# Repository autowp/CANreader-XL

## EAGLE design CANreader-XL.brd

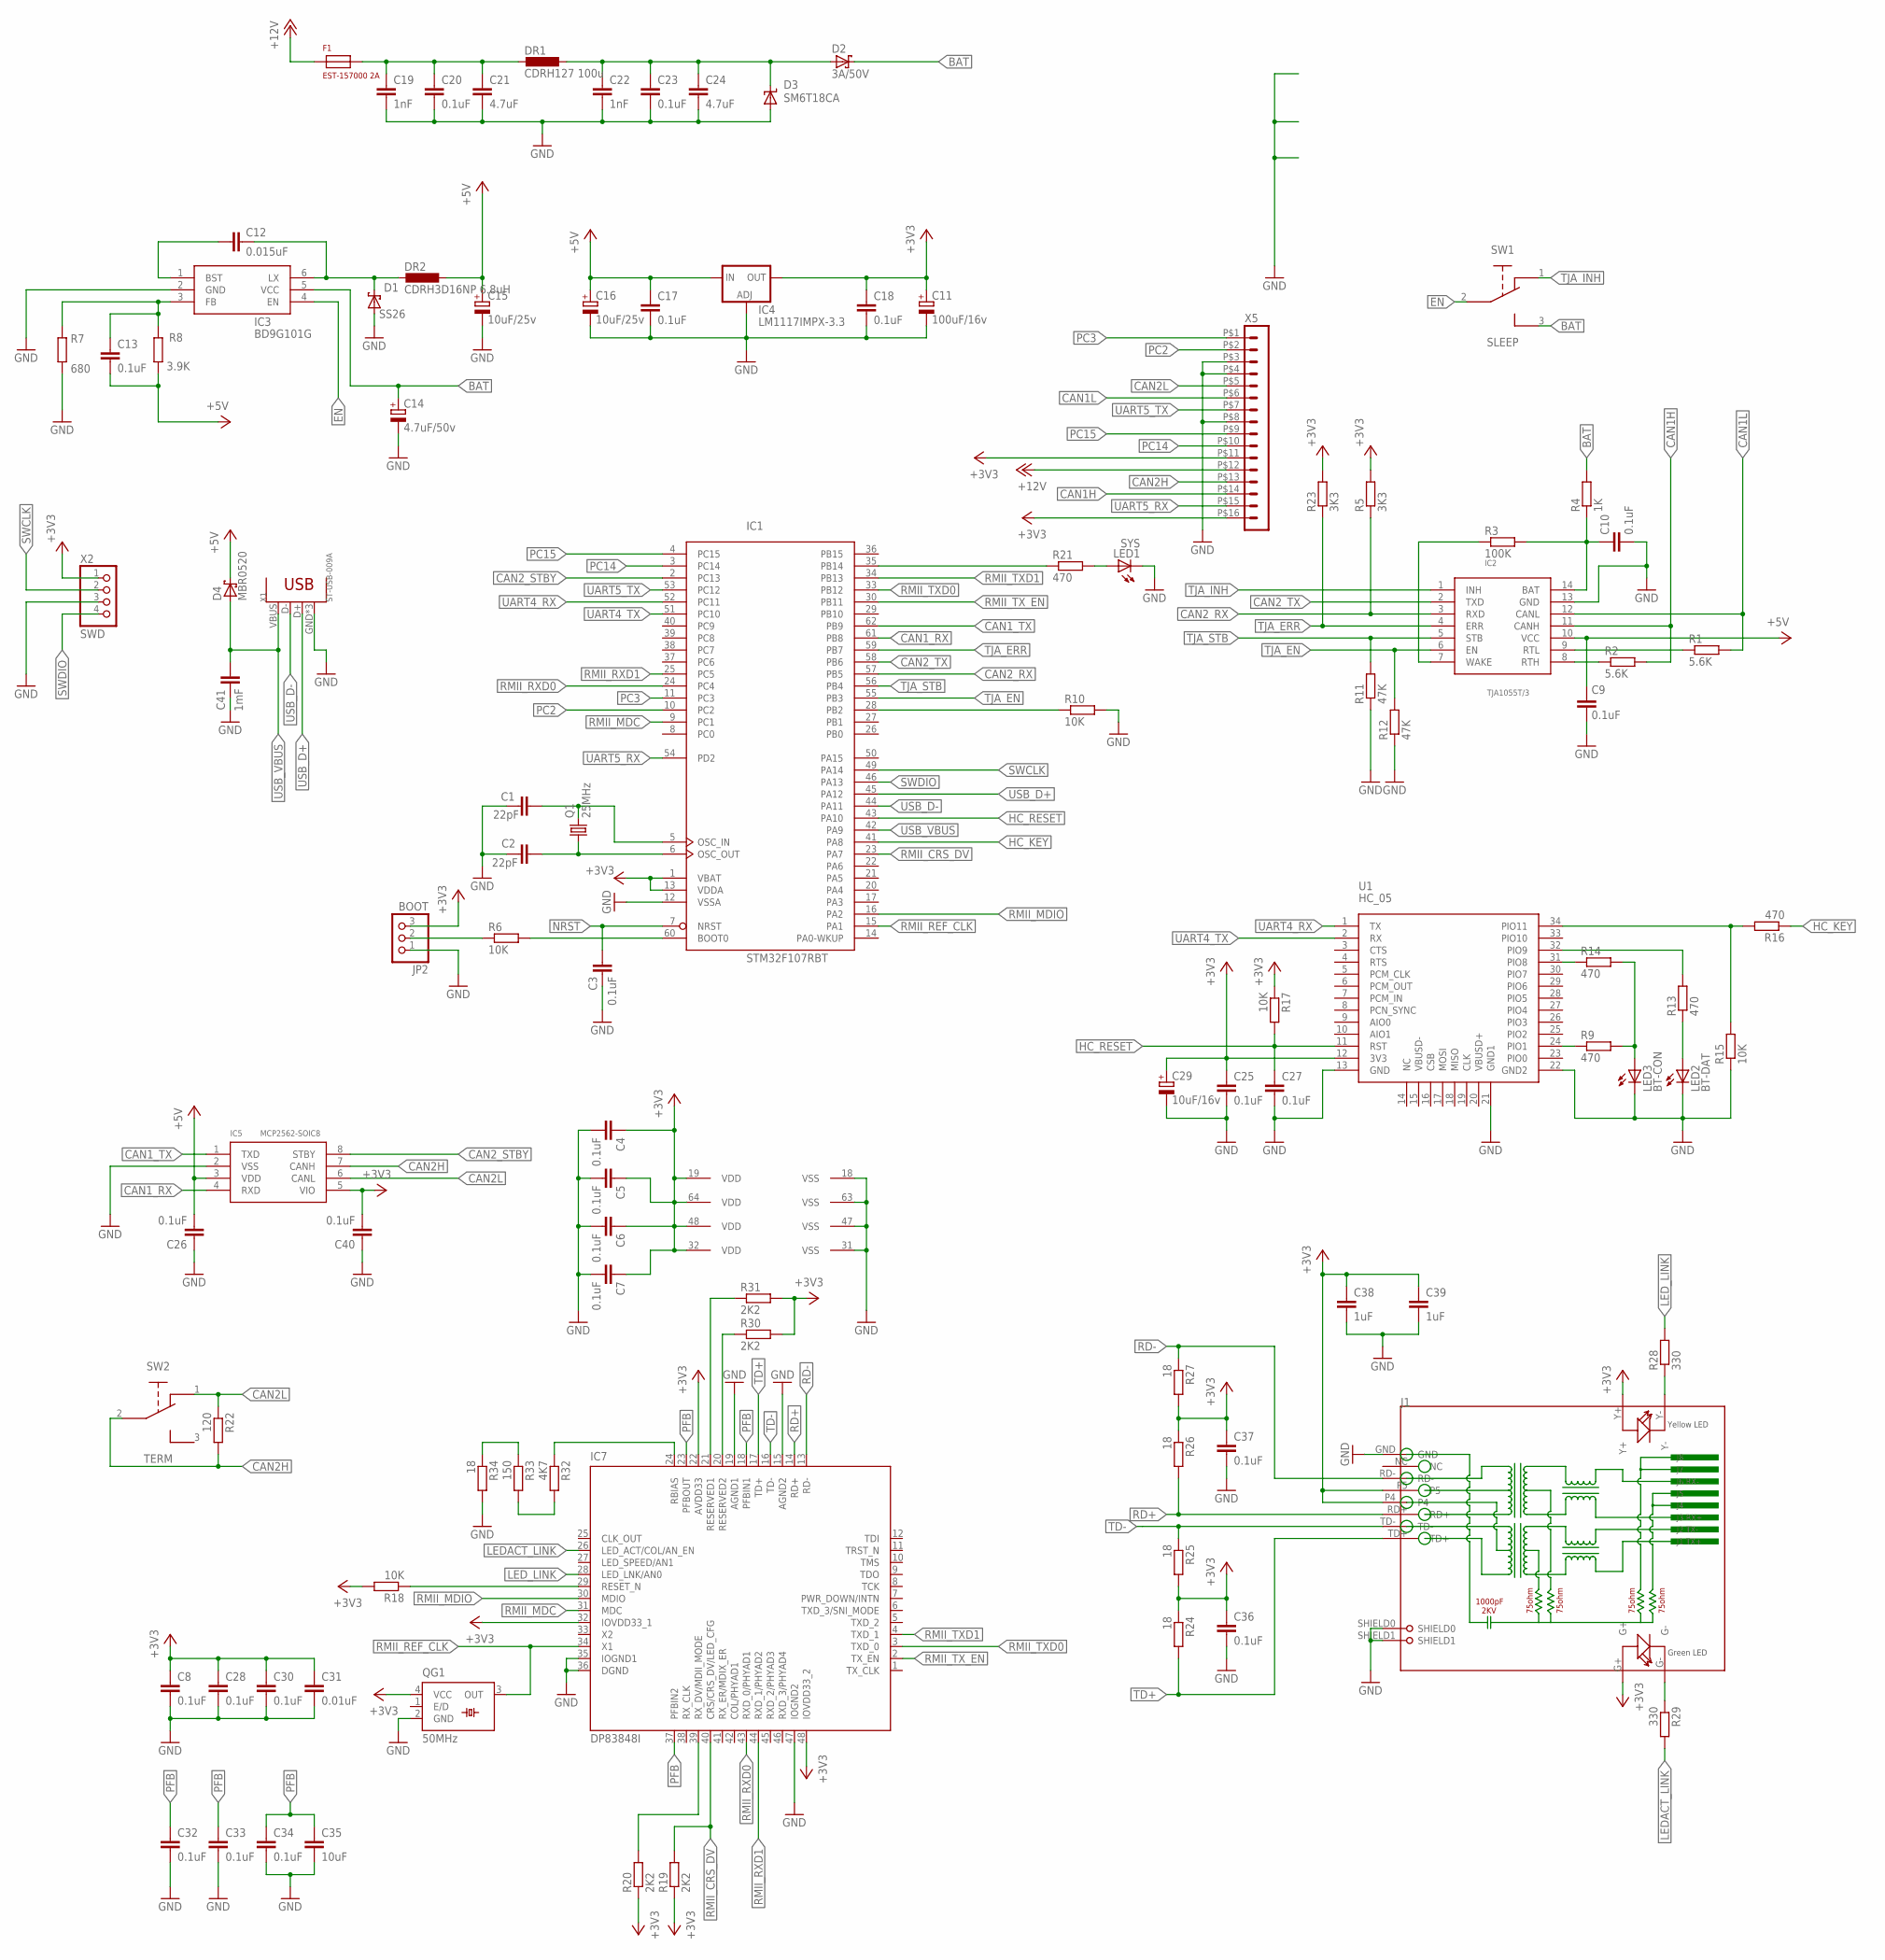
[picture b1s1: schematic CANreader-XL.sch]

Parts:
C1, C2: 22pF; C0805
C3, C4, C5, C6, C7, C8, C9, C10, C13, C17, C18, C20, C23, C25, C26, C27, C28, C30, C32, C33, C34, C36, C37, C40: 0.1uF; C0805
C11: 100uF/16v; SMC_D
C12: 0.015uF; C0805
C14: 4.7uF/50v; 153CLV-0505
C15, C16: 10uF/25v; SMC_C
C19, C22: 1nF; C0805
C21, C24: 4.7uF; C0805
C29: 10uF/16v; SMC_A
C31: 0.01uF; C0805
C35: 10uF; C0805
C38, C39: 1uF; C0805
C41: 1mF; C0805
D1: SS26; SMB
D2: 3A/50V; SMC
D3: SM6T18CA; SMBJ
D4: MBR0520; SOD123
DR1: CDRH127 100u; MS85
DR2: CDRH3D16NP 6.8uH; CDRH3D16NP
F1: EST-157000 2A; FUSE
IC1: STM32F107RBT; LQFP64
IC2: TJA1055T/3; SO-14W
IC3: BD9G101G; SSOP6
IC4: LM1117IMPX-3.3; SOT223
IC5: MCP2562-SOIC8; SOIC8-1.27-5X4MM
IC7: DP83848I; LQFP48
J1: RJ45-HR911105A-HR911105A; RJ45
JP2: BOOT; 1X03
LED1: SYS; LED3MM
LED2: BT-DAT; LED3MM
LED3: BT-CON; LED3MM
Q1: 25MHz; HC49/S
QG1: 50MHz; SM77H
R1, R2: 5.6K; R0805
R3: 100K; R0805
R4: 1K; R0805
R5, R23: 3K3; R0805
R6, R10, R15, R17, R18: 10K; R0805
R7: 680; R0805
R8: 3.9K; R0805
R9, R13, R14, R16, R21: 470; R0805
R11, R12: 47K; R0805
R19, R20, R30, R31: 2K2; R0805
R22: 120; R0805
R24, R25, R26, R27, R34: 18; R0805
R28, R29: 330; R0805
R32: 4K7; R0805
R33: 150; R0805
SW1: SLEEP; SS12F27
SW2: TERM; SS12F27
U1: HC_05; BLUETOOTH_SMD
X1: ST-USB-009A; USB4+2-2.5-90D
X2: SWD; 1X04
X5: HEADER_POS16_43045-1600; 43045-1600

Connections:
+3V3: C4.1, C5.1, C6.1, C7.1, C8.1, C11.+, C18.1, C25.1, C28.1, C29.+, C30.1, C31.1, C36.1, C37.1, C38.1, C39.1, C40.2, IC1.1 (VBAT), IC1.13 (VDDA), IC1.19 (VDD), IC1.32 (VDD), IC1.48 (VDD), IC1.64 (VDD), IC4.2 (OUT), IC4.4 (OUT), IC5.5 (VIO), IC7.22 (AVDD33), IC7.32 (IOVDD33_1), IC7.48 (IOVDD33_2), J1.G+, J1.P4, J1.P5, J1.Y+, JP2.3, QG1.4 (VCC), R5.2, R17.1, R18.2, R19.1, R20.1, R23.2, R24.1, R25.2, R26.1, R27.2, R30.2, R31.2, U1.12 (3V3), X2.1, X5.P$11 (11), X5.P$16 (16)
+5V: C9.1, C13.2, C15.+, C16.+, C17.1, C26.2, D4.C, DR2.P$2 (2), IC2.10 (VCC), IC4.3 (IN), IC5.3 (VDD), R8.1
+12V: F1.P$1 (1), X5.P$12 (12)
BAT: C14.+, D2.C, IC3.5 (VCC), R4.2, SW1.3
BAT1: C22.1, C23.1, C24.1, D2.A, D3.C, DR1.P$2 (2)
BD9-FB: C13.1, IC3.3 (FB), R7.2, R8.2
CAN1H: IC2.11 (CANH), R2.2, X5.P$14 (14)
CAN1L: IC2.12 (CANL), R1.2, X5.P$6 (6)
CAN1_RX: IC1.61 (PB8), IC5.4 (RXD)
CAN1_TX: IC1.62 (PB9), IC5.1 (TXD)
CAN2H: IC5.7 (CANH), R22.2, SW2.2, X5.P$13 (13)
CAN2L: IC5.6 (CANL), R22.1, SW2.1, X5.P$5 (5)
CAN2_RX: IC1.57 (PB5), IC2.3 (RXD), R5.1
CAN2_STBY: IC1.2 (PC13), IC5.8 (STBY)
CAN2_TX: IC1.58 (PB6), IC2.2 (TXD)
EN: IC3.4 (EN), SW1.2
GND: C1.2, C2.2, C3.1, C4.2, C5.2, C6.2, C7.2, C8.2, C9.2, C10.2, C11.-, C14.-, C15.-, C16.-, C17.2, C18.2, C19.2, C20.2, C21.2, C22.2, C23.2, C24.2, C25.2, C26.1, C27.2, C28.2, C29.-, C30.2, C31.2, C32.2, C33.2, C34.2, C35.2, C36.2, C37.2, C38.2, C39.2, C40.1, C41.2, D1.A, D3.A, IC1.12 (VSSA), IC1.18 (VSS), IC1.31 (VSS), IC1.47 (VSS), IC1.63 (VSS), IC2.13 (GND), IC3.2 (GND), IC4.1 (ADJ), IC5.2 (VSS), IC7.15 (AGND2), IC7.19 (AGND1), IC7.35 (IOGND1), IC7.36 (DGND), IC7.47 (IOGND2), J1.GND, J1.SHIELD0, J1.SHIELD1, JP2.1, LED1.K (C), LED2.K (C), LED3.K (C), QG1.2 (GND), R7.1, R10.2, R11.1, R12.1, R15.1, R34.2, U1.13 (GND), U1.21 (GND1), U1.22 (GND2), X1.GND (4), X1.S1 (4), X1.S2 (4), X2.3, X5.P$3 (3), X5.P$4 (4), X5.P$8 (8)
HC_KEY: IC1.41 (PA8), R16.1
HC_RESET: C27.1, IC1.43 (PA10), R17.2, U1.11 (RST)
LEDACT_LINK: IC7.26 (LED_ACT/COL/AN_EN), R29.2
LED_LINK: IC7.28 (LED_LNK/AN0), R28.2
unnamed: C1.1, IC1.5 (OSC_IN), Q1.2
unnamed: C2.1, IC1.6 (OSC_OUT), Q1.1
unnamed: IC1.60 (BOOT0), R6.2
unnamed: IC1.28 (PB2), R10.1
unnamed: R14.1, U1.31 (PIO8)
unnamed: IC1.35 (PB14), R21.1
unnamed: IC2.8 (RTH), R2.1
unnamed: IC2.9 (RTL), R1.1
unnamed: C12.1, IC3.1 (BST)
unnamed: R13.2, U1.32 (PIO9)
unnamed: LED2.A, R13.1
unnamed: C12.2, D1.C, DR2.P$1 (1), IC3.6 (LX)
unnamed: R9.1, U1.24 (PIO1)
unnamed: LED1.A, R21.2
unnamed: IC7.29 (RESET_N), R18.1
unnamed: IC7.20 (RESERVED2), R30.1
unnamed: C19.1, C20.1, C21.1, DR1.P$1 (1), F1.P$2 (2)
unnamed: IC7.39 (RX_DV/MDII_MODE), R20.2
unnamed: IC7.21 (RESERVED1), R31.1
unnamed: J1.G-, R29.1
unnamed: J1.Y-, R28.1
unnamed: R15.2, R16.2, U1.34 (PIO11)
unnamed: IC7.24 (RBIAS), R32.1
unnamed: R32.2, R33.2
unnamed: R33.1, R34.1
unnamed: JP2.2, R6.1
unnamed: LED3.A, R9.2, R14.2
NRST: C3.2, IC1.7 (NRST)
PC2: IC1.10 (PC2), X5.P$2 (2)
PC3: IC1.11 (PC3), X5.P$1 (1)
PC14: IC1.3 (PC14), X5.P$10 (10)
PC15: IC1.4 (PC15), X5.P$9 (9)
PFB: C32.1, C33.1, C34.1, C35.1, IC7.18 (PFBIN1), IC7.23 (PFBOUT), IC7.37 (PFBIN2)
RD+: IC7.14 (RD+), J1.RD+, R26.2
RD-: IC7.13 (RD-), J1.RD-, R27.1
RMII_CRS_DV: IC1.23 (PA7), IC7.40 (CRS/CRS_DV/LED_CFG), R19.2
RMII_MDC: IC1.9 (PC1), IC7.31 (MDC)
RMII_MDIO: IC1.16 (PA2), IC7.30 (MDIO)
RMII_REF_CLK: IC1.15 (PA1), IC7.34 (X1), QG1.3 (OUT)
RMII_RXD0: IC1.24 (PC4), IC7.43 (RXD_0/PHYAD1)
RMII_RXD1: IC1.25 (PC5), IC7.44 (RXD_1/PHYAD2)
RMII_TXD0: IC1.33 (PB12), IC7.3 (TXD_0)
RMII_TXD1: IC1.34 (PB13), IC7.4 (TXD_1)
RMII_TX_EN: IC1.30 (PB11), IC7.2 (TX_EN)
SWCLK: IC1.49 (PA14), X2.2
SWDIO: IC1.46 (PA13), X2.4
TD+: IC7.17 (TD+), J1.TD+, R24.2
TD-: IC7.16 (TD-), J1.TD-, R25.1
TJABAT: C10.1, IC2.14 (BAT), R3.2, R4.1
TJAWAKE: IC2.7 (WAKE), R3.1
TJA_EN: IC1.55 (PB3), IC2.6 (EN), R12.2
TJA_ERR: IC1.59 (PB7), IC2.4 (ERR), R23.1
TJA_INH: IC2.1 (INH), SW1.1
TJA_STB: IC1.56 (PB4), IC2.5 (STB), R11.2
UART4_RX: IC1.52 (PC11), U1.1 (TX)
UART4_TX: IC1.51 (PC10), U1.2 (RX)
UART5_RX: IC1.54 (PD2), X5.P$15 (15)
UART5_TX: IC1.53 (PC12), X5.P$7 (7)
USB_D+: IC1.45 (PA12), X1.D+ (3)
USB_D-: IC1.44 (PA11), X1.D- (2)
USB_VBUS: C41.1, D4.A, IC1.42 (PA9), X1.VBUS (1)

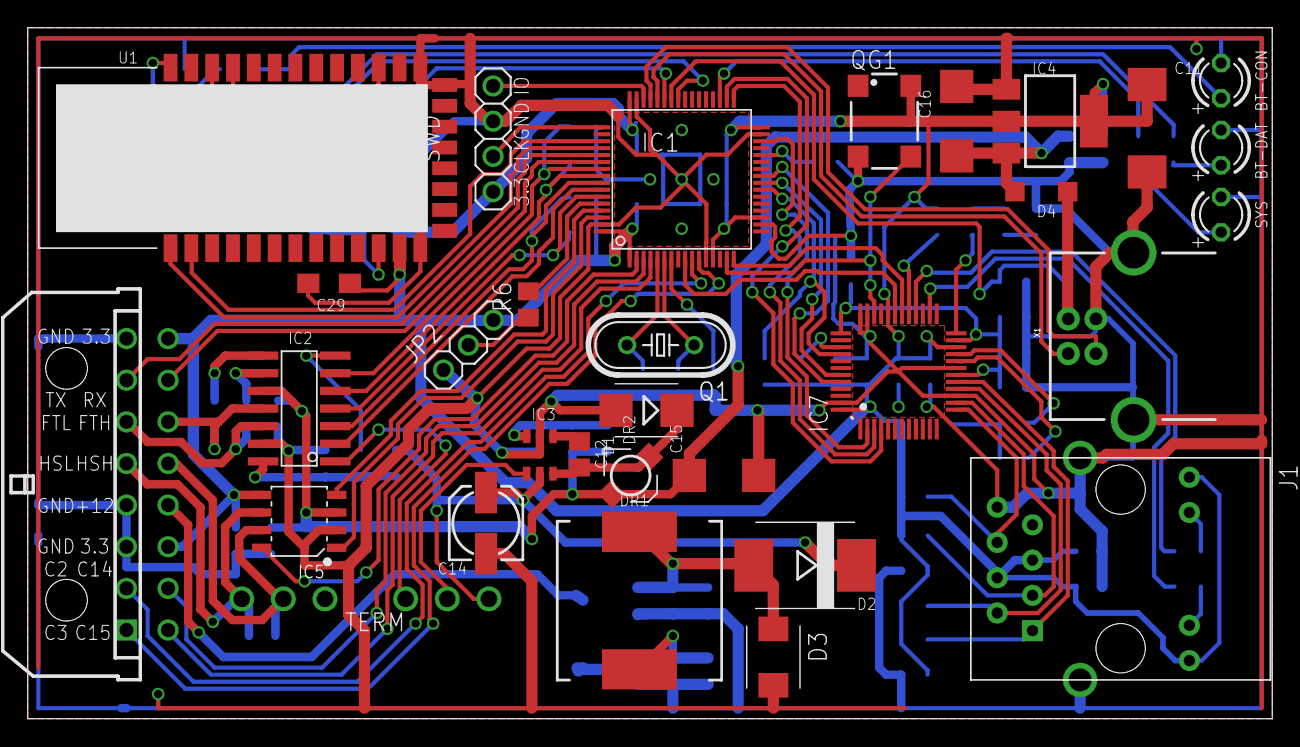
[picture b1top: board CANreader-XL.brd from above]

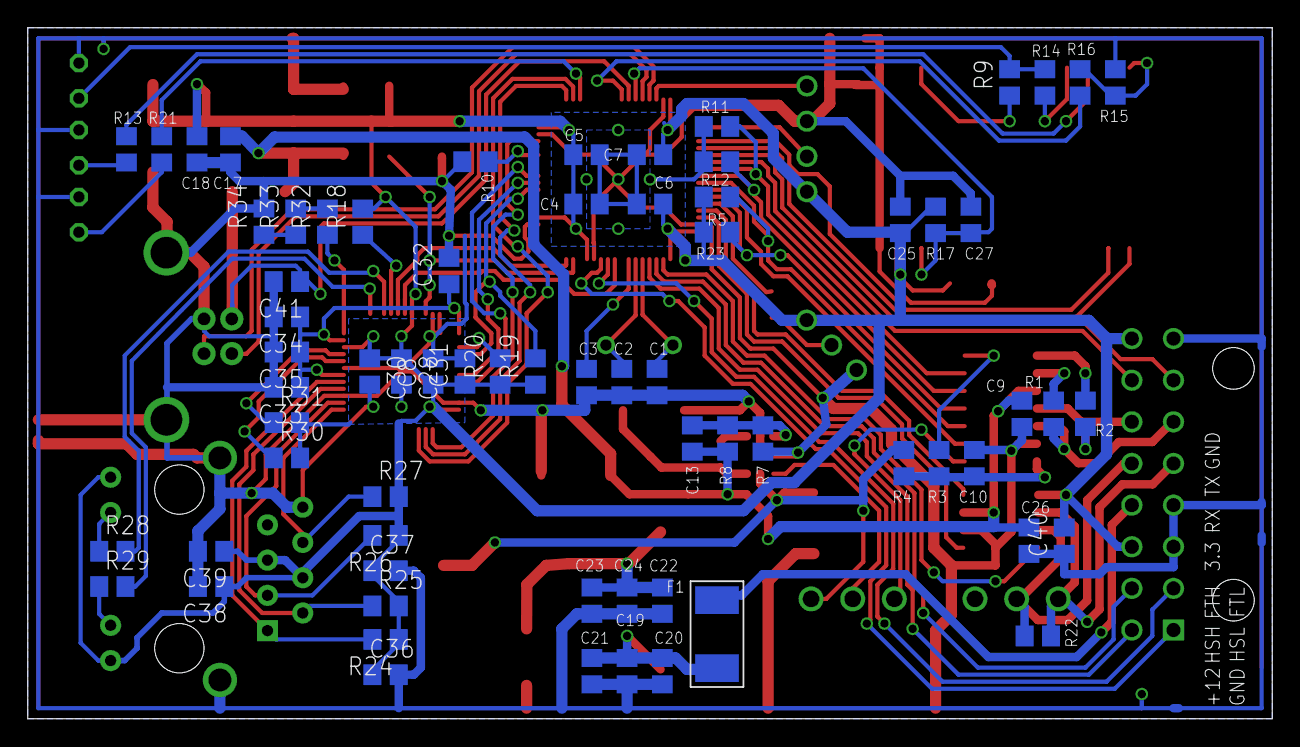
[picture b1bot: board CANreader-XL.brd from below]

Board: 2 copper layers, 89.7 x 49.8 mm, 101 parts (69 on the bottom side), 82 nets.

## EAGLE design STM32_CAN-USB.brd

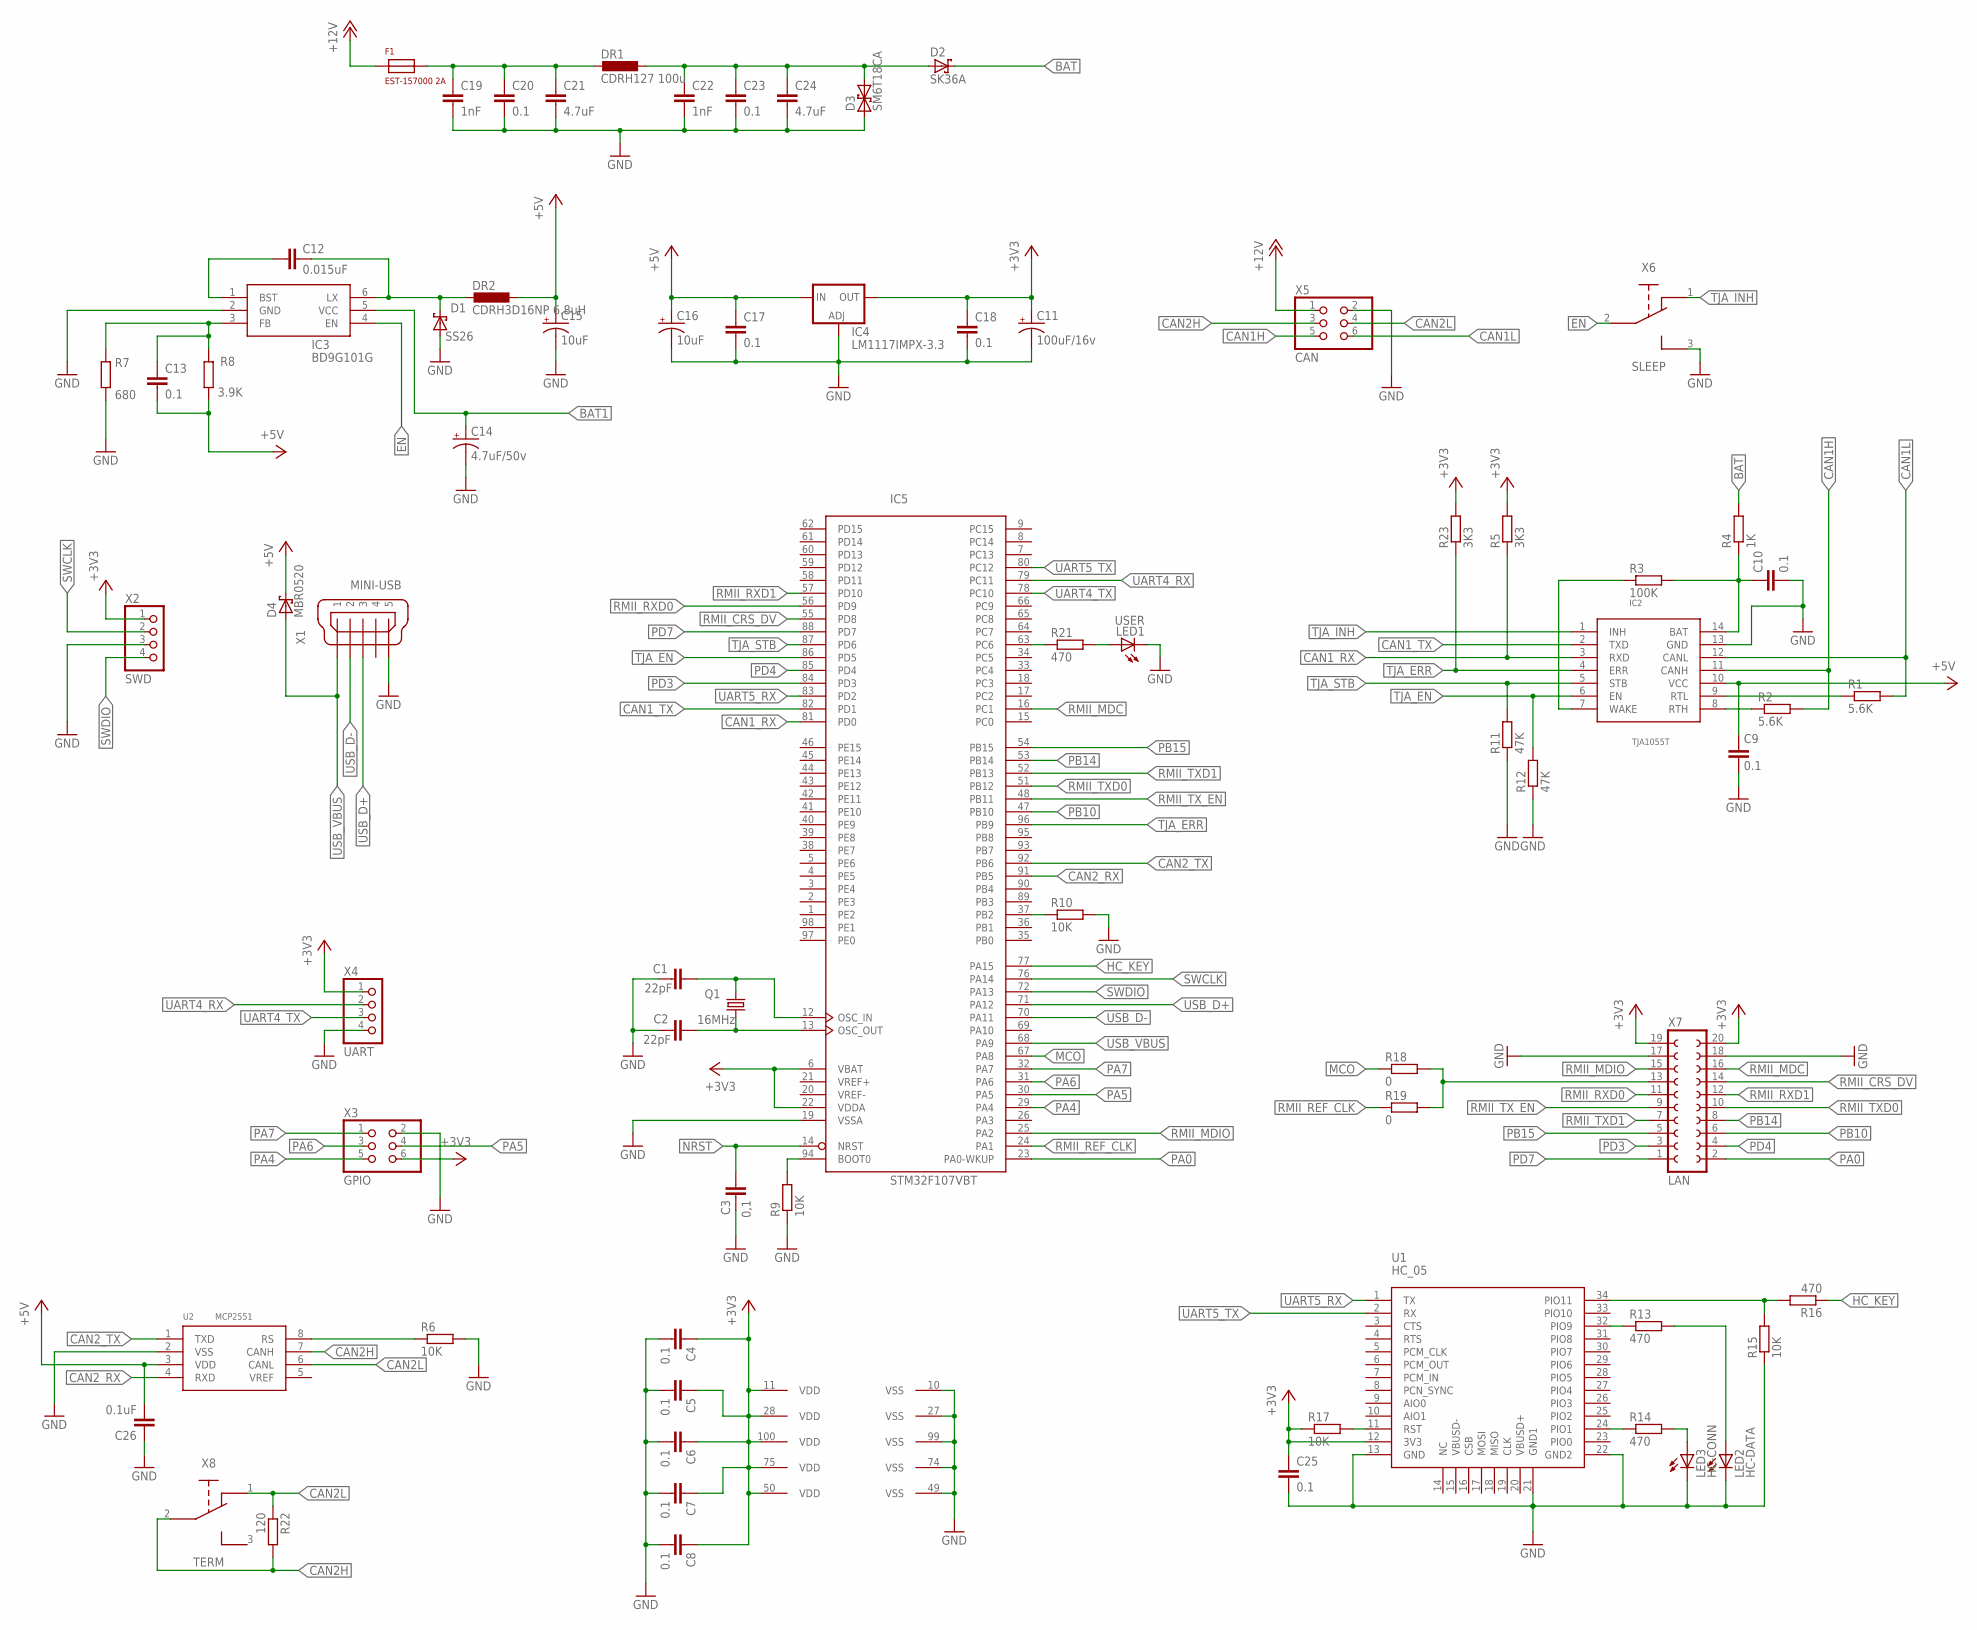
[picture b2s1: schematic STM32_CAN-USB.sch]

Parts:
C1, C2: 22pF; C0805
C3: 0,1; C0805
C4, C5, C6, C7, C8, C9, C10, C13, C17, C18, C20, C23, C25: 0.1; C0805
C11: 100uF/16v; 153CLV-0605
C12: 0.015uF; C0805
C14: 4.7uF/50v; 153CLV-0605
C15, C16: 10uF; 153CLV-0605
C19, C22: 1nF; C0805
C21, C24: 4.7uF; C0805
C26: 0.1uF; C0805
D1: SS26; SMB
D2: SK36A; DO-214AC
D3: SM6T18CA; DO214AA
D4: MBR0520; SOD123
DR1: CDRH127 100u; MS85
DR2: CDRH3D16NP 6.8uH; CDRH3D16NP
F1: EST-157000 2A; FUSE
IC2: TJA1055T; SO-14W
IC3: BD9G101G; SSOP6
IC4: LM1117IMPX-3.3; SOT223
IC5: STM32F107VBT; LQFP100
LED1: USER; LED3MM
LED2: HC-DATA; LED3MM
LED3: HC-CONN; LED3MM
Q1: 16MHz; HC49UP
R1, R2: 5.6K; R0805
R3: 100K; R0805
R4: 1K; R0805
R5, R23: 3K3; R0805
R6, R9, R10, R15, R17: 10K; R0805
R7: 680; R0805
R8: 3.9K; R0805
R11, R12: 47K; R0805
R13, R14, R16, R21: 470; R0805
R18, R19: 0; R0805
R22: 120; R0805
U1: HC_05; BLUETOOTH_SMD
U2: MCP2551; SO08
X1: MINI-USB; UX60-MB-5ST
X2: SWD; 1X04
X3: GPIO; 2X03/90
X4: UART; 1X04/90
X5: CAN; 2X03/90
X6: SLEEP; SS12F27
X7: LAN; FE10-2W
X8: TERM; SS12F27

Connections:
+3V3: C4.1, C5.1, C6.1, C7.1, C8.1, C11.+, C18.1, C25.1, IC4.2 (OUT), IC4.4 (OUT), IC5.6 (VBAT), IC5.11 (VDD), IC5.22 (VDDA), IC5.28 (VDD), IC5.50 (VDD), IC5.75 (VDD), IC5.100 (VDD), R5.2, R17.1, R23.2, U1.12 (3V3), X2.1, X3.6, X4.1, X7.19, X7.20
+5V: C9.1, C13.2, C15.+, C16.+, C17.1, C26.2, D4.C, DR2.P$2 (2), IC2.10 (VCC), IC4.3 (IN), R8.1, U2.3 (VDD)
+12V: F1.P$1 (1), X5.1
BAT: D2.C, R4.2
BAT1: C14.+, C22.1, C23.1, C24.1, D2.A, D3.C (2), DR1.P$2 (2), IC3.5 (VCC)
BD9-FB: C13.1, IC3.3 (FB), R7.2, R8.2
CAN1H: IC2.11 (CANH), R2.2, X5.5
CAN1L: IC2.12 (CANL), R1.2, X5.6
CAN1_RX: IC2.3 (RXD), IC5.81 (PD0), R5.1
CAN1_TX: IC2.2 (TXD), IC5.82 (PD1)
CAN2H: R22.2, U2.7 (CANH), X5.3, X8.2
CAN2L: R22.1, U2.6 (CANL), X5.4, X8.1
CAN2_RX: IC5.91 (PB5), U2.4 (RXD)
CAN2_TX: IC5.92 (PB6), U2.1 (TXD)
EN: IC3.4 (EN), X6.2
GND: C1.2, C2.2, C3.1, C4.2, C5.2, C6.2, C7.2, C8.2, C9.2, C10.2, C11.-, C14.-, C15.-, C16.-, C17.2, C18.2, C19.2, C20.2, C21.2, C22.2, C23.2, C24.2, C25.2, C26.1, D1.A, D3.A (1), IC2.13 (GND), IC3.2 (GND), IC4.1 (ADJ), IC5.10 (VSS), IC5.19 (VSSA), IC5.27 (VSS), IC5.49 (VSS), IC5.74 (VSS), IC5.99 (VSS), LED1.K (C), LED2.K (C), LED3.K (C), R6.2, R7.1, R9.1, R10.2, R11.1, R12.1, R15.1, U1.13 (GND), U1.21 (GND1), U1.22 (GND2), U2.2 (VSS), X1.5, X1.M1 (5), X1.M2 (5), X2.3, X3.2, X4.4, X5.2, X6.3, X7.17, X7.18
HC_KEY: IC5.77 (PA15), R16.1
MCO: IC5.67 (PA8), R18.1
unnamed: C1.1, IC5.12 (OSC_IN), Q1.2
unnamed: C2.1, IC5.13 (OSC_OUT), Q1.1
unnamed: IC5.94 (BOOT0), R9.2
unnamed: IC5.37 (PB2), R10.1
unnamed: R6.1, U2.8 (RS)
unnamed: IC5.63 (PC6), R21.1
unnamed: IC2.8 (RTH), R2.1
unnamed: IC2.9 (RTL), R1.1
unnamed: C12.1, IC3.1 (BST)
unnamed: C12.2, D1.C, DR2.P$1 (1), IC3.6 (LX)
unnamed: LED1.A, R21.2
unnamed: C19.1, C20.1, C21.1, DR1.P$1 (1), F1.P$2 (2)
unnamed: R13.1, U1.32 (PIO9)
unnamed: R14.1, U1.24 (PIO1)
unnamed: LED2.A, R13.2
unnamed: LED3.A, R14.2
unnamed: R17.2, U1.11 (RST)
unnamed: R15.2, R16.2, U1.34 (PIO11)
unnamed: R18.2, R19.2, X7.13
NRST: C3.2, IC5.14 (NRST)
PA0: IC5.23 (PA0-WKUP), X7.2
PA4: IC5.29 (PA4), X3.5
PA5: IC5.30 (PA5), X3.4
PA6: IC5.31 (PA6), X3.3
PA7: IC5.32 (PA7), X3.1
PB10: IC5.47 (PB10), X7.6
PB14: IC5.53 (PB14), X7.8
PB15: IC5.54 (PB15), X7.5
PD3: IC5.84 (PD3), X7.3
PD4: IC5.85 (PD4), X7.4
PD7: IC5.88 (PD7), X7.1
RMII_CRS_DV: IC5.55 (PD8), X7.14
RMII_MDC: IC5.16 (PC1), X7.16
RMII_MDIO: IC5.25 (PA2), X7.15
RMII_REF_CLK: IC5.24 (PA1), R19.1
RMII_RXD0: IC5.56 (PD9), X7.11
RMII_RXD1: IC5.57 (PD10), X7.12
RMII_TXD0: IC5.51 (PB12), X7.10
RMII_TXD1: IC5.52 (PB13), X7.7
RMII_TX_EN: IC5.48 (PB11), X7.9
SWCLK: IC5.76 (PA14), X2.2
SWDIO: IC5.72 (PA13), X2.4
TJABAT: C10.1, IC2.14 (BAT), R3.2, R4.1
TJAWAKE: IC2.7 (WAKE), R3.1
TJA_EN: IC2.6 (EN), IC5.86 (PD5), R12.2
TJA_ERR: IC2.4 (ERR), IC5.96 (PB9), R23.1
TJA_INH: IC2.1 (INH), X6.1
TJA_STB: IC2.5 (STB), IC5.87 (PD6), R11.2
UART4_RX: IC5.79 (PC11), X4.2
UART4_TX: IC5.78 (PC10), X4.3
UART5_RX: IC5.83 (PD2), U1.1 (TX)
UART5_TX: IC5.80 (PC12), U1.2 (RX)
USB_D+: IC5.71 (PA12), X1.3
USB_D-: IC5.70 (PA11), X1.2
USB_VBUS: D4.A, IC5.68 (PA9), X1.1
VREF+: IC5.21 (VREF+)
VREF-: IC5.20 (VREF-)

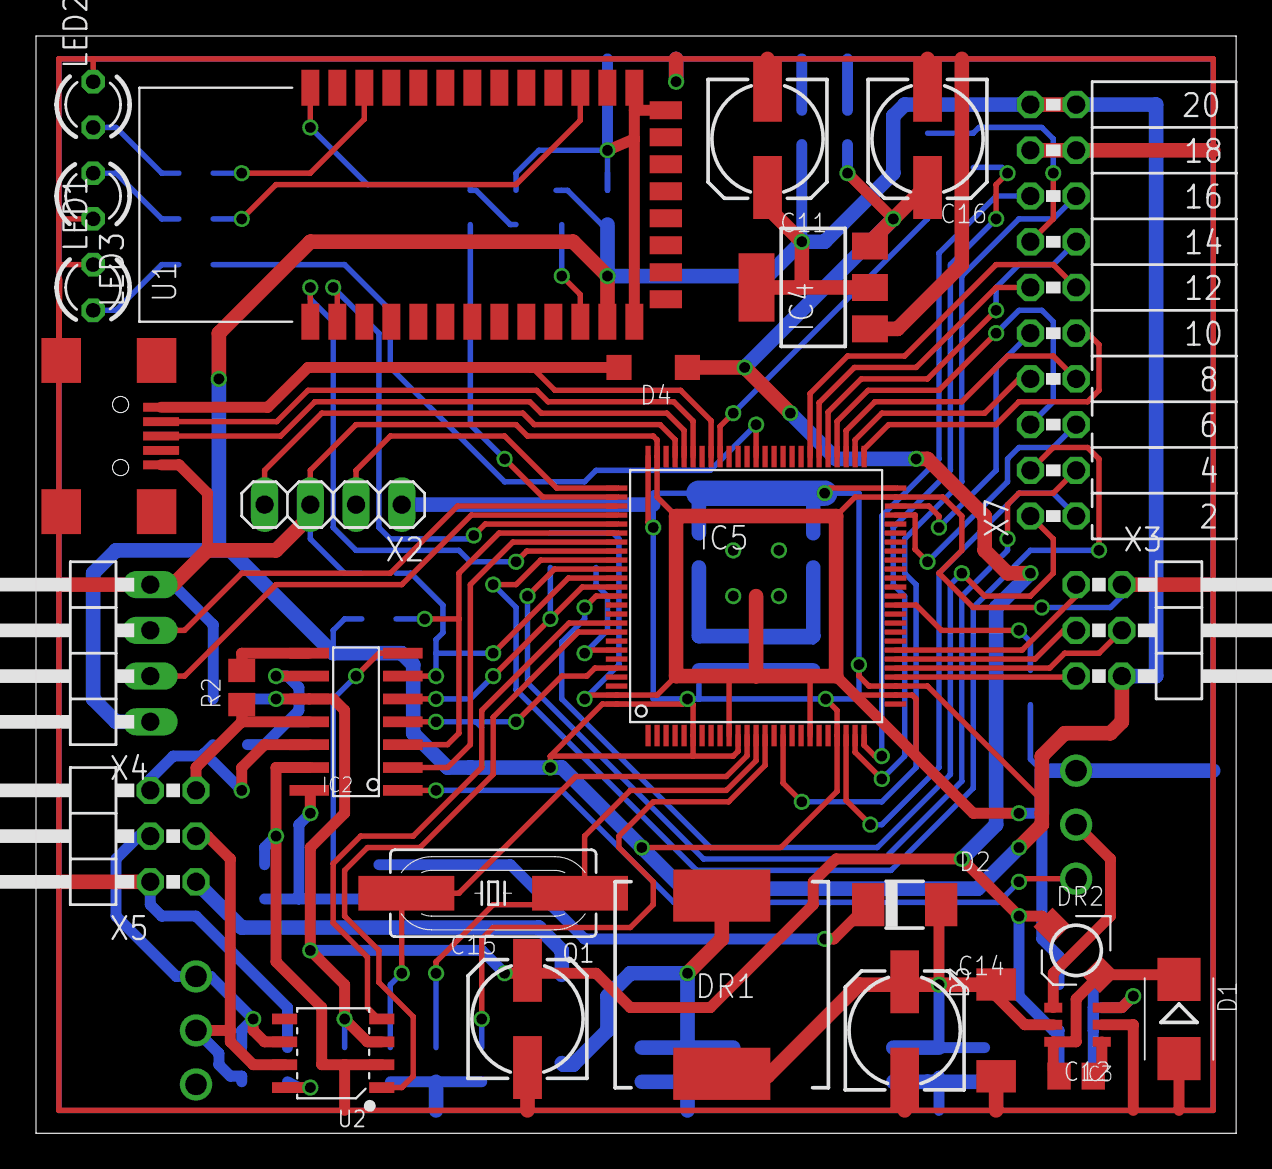
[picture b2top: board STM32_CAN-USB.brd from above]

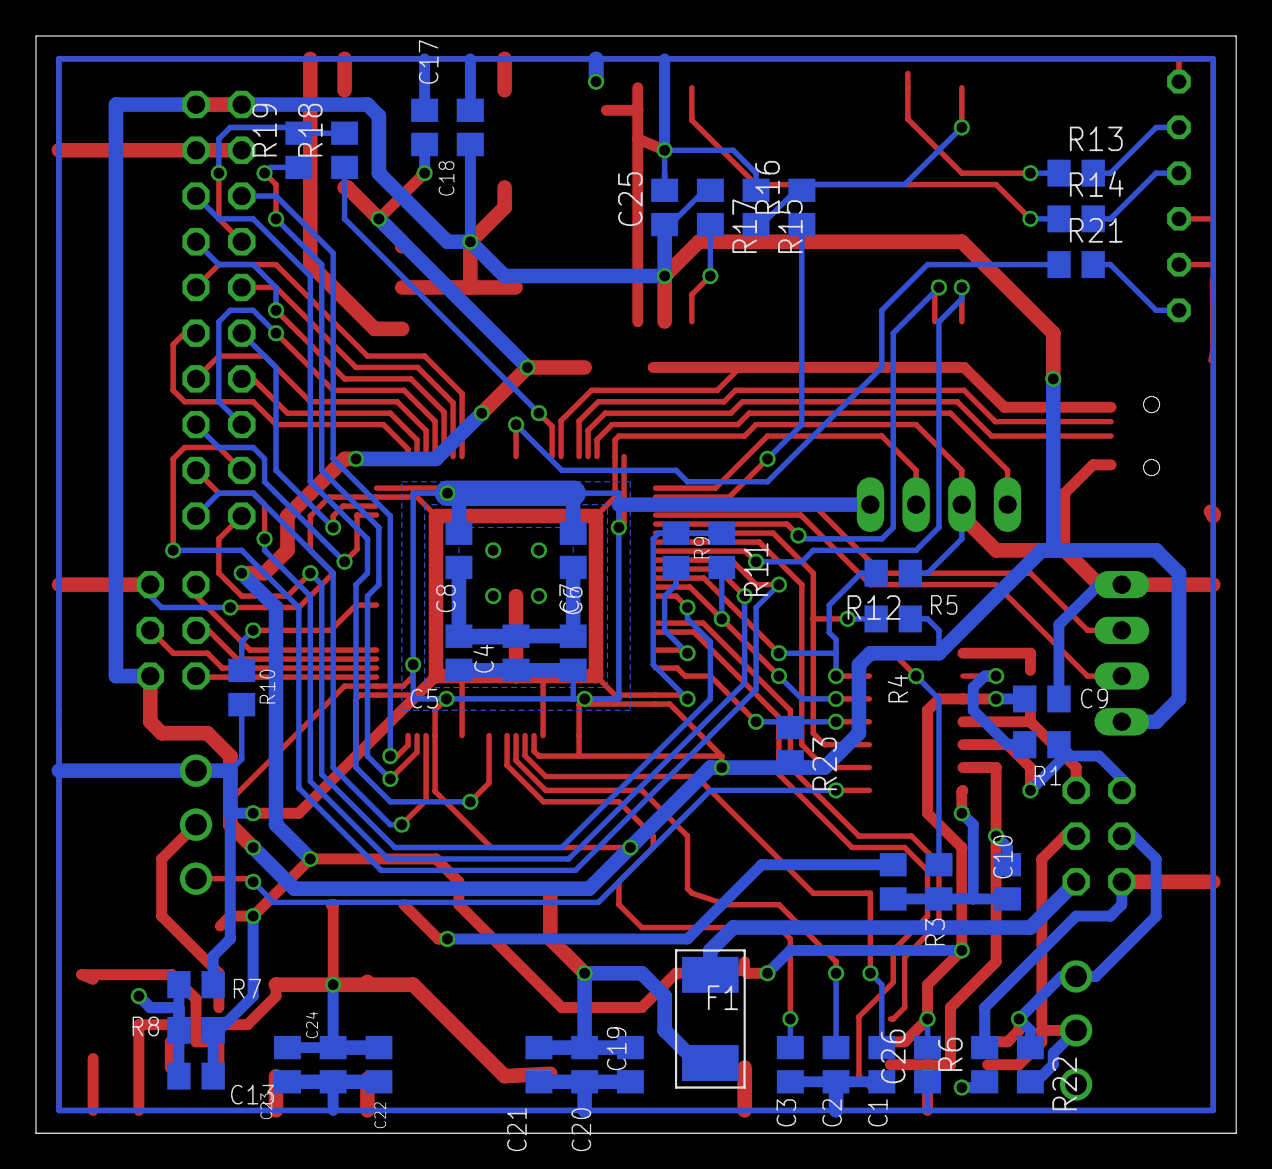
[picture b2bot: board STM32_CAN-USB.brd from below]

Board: 2 copper layers, 66.7 x 61.0 mm, 73 parts (43 on the bottom side), 73 nets.

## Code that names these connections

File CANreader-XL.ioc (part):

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Mcu.Name=STM32F107V(B-C)Tx
Mcu.Package=LQFP100
Mcu.UserName=STM32F107VBTx
PA1.Mode=RMII
PA1.Signal=ETH_REF_CLK
PA10.GPIOParameters=GPIO_Label
PA10.GPIO_Label=HC_RESET
PA10.Signal=GPIO_Output
PA11.Mode=Device_Only
PA11.Signal=USB_OTG_FS_DM
PA12.Mode=Device_Only
PA12.Signal=USB_OTG_FS_DP
PA13.Mode=Serial_Wire
PA13.Signal=SYS_JTMS-SWDIO
PA14.Mode=Serial_Wire
PA14.Signal=SYS_JTCK-SWCLK
PA15.GPIOParameters=GPIO_Label
PA15.GPIO_Label=HC_KEY
PA15.Signal=GPIO_Output
PA2.Mode=RMII
PA2.Signal=ETH_MDIO
PA4.Signal=GPIO_Output
PA5.Signal=GPIO_Output
PA6.Signal=GPIO_Output
PA7.Signal=GPIO_Output
PA9.Mode=Activate_VBUS
PA9.Signal=USB_OTG_FS_VBUS
PB10.GPIOParameters=GPIO_Label
PB10.GPIO_Label=LAN_PB10
PB10.Signal=GPIO_Output
PB11.Mode=RMII
PB11.Signal=ETH_TX_EN
PB12.Mode=RMII
PB12.Signal=ETH_TXD0
PB13.Mode=RMII
PB13.Signal=ETH_TXD1
PB14.GPIOParameters=GPIO_Label
PB14.GPIO_Label=LAN_PB14
PB14.Signal=GPIO_Output
PB15.GPIOParameters=GPIO_Label
PB15.GPIO_Label=LAN_PB15
PB15.Signal=GPIO_Output
PB5.Mode=Slave
PB5.Signal=CAN2_RX
PB6.Mode=Slave
PB6.Signal=CAN2_TX
PB9.GPIOParameters=GPIO_Label
PB9.GPIO_Label=TJA_ERR
PB9.Signal=GPIO_Output
PC1.Mode=RMII
PC1.Signal=ETH_MDC
PC10.Mode=Asynchronous
PC10.Signal=UART4_TX
PC11.Mode=Asynchronous
PC11.Signal=UART4_RX
PC12.Mode=Asynchronous
PC12.Signal=UART5_TX
PC6.GPIOParameters=GPIO_Label
PC6.GPIO_Label=LED
PC6.Signal=GPIO_Output
PD0.Mode=Master
PD0.Signal=CAN1_RX
PD1.Mode=Master
PD1.Signal=CAN1_TX
PD10.Mode=RMII
PD10.Signal=ETH_RXD1
PD2.Mode=Asynchronous
PD2.Signal=UART5_RX
PD3.GPIOParameters=GPIO_Label
PD3.GPIO_Label=LAN_PD3
PD3.Signal=GPIO_Output
PD4.GPIOParameters=GPIO_Label
PD4.GPIO_Label=LAN_PD4
PD4.Signal=GPIO_Output
PD5.GPIOParameters=GPIO_Label
PD5.GPIO_Label=TJA_EN
PD5.Signal=GPIO_Output
PD6.GPIOParameters=GPIO_Label
PD6.GPIO_Label=TJA_STB
PD6.Signal=GPIO_Output
PD8.Mode=RMII
PD8.Signal=ETH_CRS_DV
PD9.Mode=RMII
PD9.Signal=ETH_RXD0
RCC.HSEDivPLL=RCC_HSE_PREDIV_DIV2
RCC.HSE_VALUE=16000000
RCC.SYSCLKFreq_VALUE=72000000
RCC.SYSCLKSource=RCC_SYSCLKSOURCE_PLLCLK

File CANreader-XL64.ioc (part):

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Mcu.Name=STM32F107R(B-C)Tx
Mcu.Package=LQFP64
Mcu.UserName=STM32F107RCTx
PA1.Mode=RMII
PA1.Signal=ETH_REF_CLK
PA10.GPIOParameters=GPIO_Label
PA10.GPIO_Label=HC_RESET
PA10.Signal=GPIO_Output
PA11.Mode=Device_Only
PA11.Signal=USB_OTG_FS_DM
PA12.Mode=Device_Only
PA12.Signal=USB_OTG_FS_DP
PA13.Mode=Serial_Wire
PA13.Signal=SYS_JTMS-SWDIO
PA14.Mode=Serial_Wire
PA14.Signal=SYS_JTCK-SWCLK
PA2.Mode=RMII
PA2.Signal=ETH_MDIO
PA7.Mode=RMII
PA7.Signal=ETH_CRS_DV
PA8.GPIOParameters=GPIO_Label
PA8.GPIO_Label=HC_KEY
PA8.Signal=GPIO_Output
PA9.Mode=Activate_VBUS
PA9.Signal=USB_OTG_FS_VBUS
PB11.Mode=RMII
PB11.Signal=ETH_TX_EN
PB12.Mode=RMII
PB12.Signal=ETH_TXD0
PB13.Mode=RMII
PB13.Signal=ETH_TXD1
PB14.GPIOParameters=GPIO_Label
PB14.GPIO_Label=LED
PB14.Signal=GPIO_Output
PB2.GPIOParameters=GPIO_Label
PB2.GPIO_Label=BOOT1
PB2.Signal=GPIO_Input
PB3.GPIOParameters=GPIO_Label
PB3.GPIO_Label=TJA_EN
PB3.Signal=GPIO_Output
PB4.GPIOParameters=GPIO_Label
PB4.GPIO_Label=TJA_STB
PB4.Signal=GPIO_Output
PB5.Mode=Slave
PB5.Signal=CAN2_RX
PB6.Mode=Slave
PB6.Signal=CAN2_TX
PB7.GPIOParameters=GPIO_Label
PB7.GPIO_Label=TJA_ERR
PB7.Signal=GPIO_Input
PB8.Mode=Master
PB8.Signal=CAN1_RX
PB9.Mode=Master
PB9.Signal=CAN1_TX
PC1.Mode=RMII
PC1.Signal=ETH_MDC
PC10.Mode=Asynchronous
PC10.Signal=UART4_TX
PC11.Mode=Asynchronous
PC11.Signal=UART4_RX
PC12.Mode=Asynchronous
PC12.Signal=UART5_TX
PC13-TAMPER-RTC.GPIOParameters=GPIO_Label
PC13-TAMPER-RTC.GPIO_Label=CAN2_STBY
PC13-TAMPER-RTC.Signal=GPIO_Output
PC14-OSC32_IN.Signal=GPIO_Output
PC15-OSC32_OUT.Signal=GPIO_Output
PC2.Signal=GPIO_Output
PC3.Signal=GPIO_Output
PC4.Mode=RMII
PC4.Signal=ETH_RXD0
PC5.Mode=RMII
PC5.Signal=ETH_RXD1
PD0-OSC_IN.Mode=HSE-External-Oscillator
PD0-OSC_IN.Signal=RCC_OSC_IN
PD1-OSC_OUT.Mode=HSE-External-Oscillator
PD1-OSC_OUT.Signal=RCC_OSC_OUT
PD2.Mode=Asynchronous
PD2.Signal=UART5_RX
RCC.HSEDivPLL=RCC_HSE_PREDIV_DIV5
RCC.HSE_VALUE=25000000
RCC.SYSCLKFreq_VALUE=72000000
RCC.SYSCLKSource=RCC_SYSCLKSOURCE_PLLCLK

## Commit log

2016-04-27 Rename cube file
2016-04-27 Rename Eagle files
2016-04-27 HC-05 isolation, Antenna hole
2016-04-27 gitignore, HC-05 Isolation fix
2016-04-27 Mount hole
2016-04-27 Board name & version
2016-04-28 Silk layers
2016-04-28 VREF+, VREF-
2016-04-28 Capacitors 0605 -> 0505
2016-04-28 Capacitors improvements, HC RST to CPU
2016-04-28 Move D2
2016-04-29 Connectors silk
2016-04-30 Drop old lib
2016-05-02 Resize to 50x80
2016-05-02 CAM job
2016-05-03 Capacitor values
2016-05-03 Minor fixes
2016-05-19 64-pin version initial
2016-05-19 LQFP100 -> LQFP64 in schematics
2016-05-20 Ethernet initial
2016-05-23 RJ45 connector
2016-05-24 fix sleep mode switch error
2016-05-24 Ignore out files
2016-05-24 Micro FIT library
2016-05-24 MCP2562, usb connector
2016-05-25 CAN2_STBY, Heap size
2016-05-25 Clocks
2016-05-26 Test inital routing
2016-05-29 Fix BT LED
2016-05-30 BOOT selection
2016-05-30 Swap UART, CAN for better routing
2016-05-31 Swap ports
2016-06-06 Attrmpt to route
2016-06-09 Route attempt
2016-06-10 USB VDD capacitor
2016-06-11 Change connector, route
2016-06-12 Route
